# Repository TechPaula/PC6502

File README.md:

# PC6502

My 6502 project in a PC104 like form factor.  
**This is unstable, some things work and and some don't, use at your own risk of sanity and wasted money/chips**  

## Status
2025-09-08 - PCBs ordered, Parts ordered.  

2025-09-11 - Edited the firmware based on Grant Searl's code. Created this Repository  

2025-09-20 - Version 1.0 is running with a few modifications, so I've created Version 1.1 of schematics and PCB. I've added some basic examples, currently you have to copy and paste into the serial terminal. Current memory map is the same as Grants;
0000-7FFF 32K RAM
8000-9FFF FREE SPACE (8K)
A000-BFFF SERIAL INTERFACE (minimally decoded)
C000-FFFF 16K ROM (BASIC from C000 TO DED3, serial routines FF00 to FFFF)
It's also not very stable just yet. I do sometimes get corruption in the data to/from the serial console.

2025-09-21 - Version 1.1 Schematic and PCB uploaded. A lot of changes and simplicifcation in some ways, A simpler CPU board (direct link to FT245R, 74161 removed and some tidying of tracks). Fixed a couple of floating inputs to RAM/ROM
VIA is much simpler, having just the one VIA chip. POWER board has USB-PD and a 24VDC input for higher power stuff in the future. These three PCBs have been orderred.

2025-10-02 - V1.1 CPU board needed a couple of mods, I forgot that one of the pins that I used as input before had become output but the CPLD could not support that. New CPLD code done. **Now runs with a 12MHz clock (6MHz CPU speed)**, I found without the VIA it ran with a 16MHz clock fine, but would not run with a 20MHz clock, I suspect this is down to the FT245. This may get resolved when I add clock stretching to the CPLD. **VIA V1.1 working fine!** CPU board modded and Schematics and PCB updated, CPLD code for VIA and CPU updated. Updated memory map below

2025-10-11 - Power board built, works great, however the switch is inadequate, so I've hard wired it

2025-10-14 - CPLD code for the CPU PCB updated, with help from Shonky it now runs at up to the full 14MHz and also will do clock stretching when using SLOW1 line. The SLOW0 line is still bring problematic.

2025-10-16 - SPEECH synthesis chip working fine after a couple of extra wires on V1.0 of the PCB, V1.1 has been updated with these. The OPL3 (YMF262) is reading and writing, but not yet making sound.

2025-10-19 - Dual SPI board confirmed working!
It looks like my Apple II slots might be bacwards, I need to do more checking to confirm one way or the other.
The Compact Flash Storage board is also working, at least as far as raw byte reads and reads are concerned.

2025-10-23 - OPL3 Now working! I've made a change to the PCB and Schematics to fix the problem.
The CPU Board has also had a change this allows Clock stretching to be added. Currently only the SLOW1 input is working, but I will add the other later.
CPLD code for the compact flash board, updated VIA CPLD code and updated CPU CPLD code are now in.

2025-11-02 - Finished the Rev 1.0 keyboard and interface cards, I also made a simple 5V PMOD level shifter. these have been ordered.
Still testing the AII SLOT PCB, I'm unsure if it is working 100% or not, needs more time and ideally an apple II card to test with.

2025-11-12 - Working on KeyBed code.

2025-11-15 - Updated the KeyTFT board to Rev 1.1, removed the ATMEGA644, replaced it with a W65C51, as it'll only really be receiving from the keyboard I'm hoping the bug won't be a problem. The display is also now parallel rather than SPI.
Addtionally I've tweaked the CPU board to revision 1.4, this connects A15 direct to the RAM, so in theory getting more than 32K should be quicker and just require a change in the CPLD.
Keybed code working, aside from caps lock. Waiting for the full keyset and stabalisers to arrive before doing more.

2025-11-17 - EhBASIC and WozMon enhanced are now up and running on the PC6502 thanks to Shonky. EhBASIC is a little faster, but for me this brings a much needed ability to work with values in hex ($) or binary (%) which makes life a lot easier when trying to drive peripherals and IO.

2025-12-6 - I managed to get text and graphics on the display (image below), I still can't get a single pixel to work, so I'm currently using really short lines. next up will be the keyboard serial interface.

## CPU Board
Actual PCB:

Mandlebrot Code:

This board has a 6502, RAM and ROM on board, along with an ATF1502 for address decoding. There is also an FT245R which is pretending to be a 68B50 with USB. 
The CPLD code and .JED files are in /Software/CPLD

## VIA Board
This board has a single 6522 VIA and an ATF1502 for address decoding, The VIA outputs are brought out to PMOD style headers (though are 5V)
The CPLD code and .JED files are in /Software/CPLD

## Dual SPI board
Featuring two SPI interfaces, based on https://sbc.rictor.org/65spi2.html.
This uses two ATF1504AS and a single ATF1502AS.
(Note: in the picture I'm using the wrong ATF1504s, oops)

## Compact Flash board
A Very simple board in terms of electronics. Reading and Writing raw bytes is working!.

## FM(OPL3) and SPEECH card
So far the speech engine is working great, and I can read/write from/to the OPL3, I can't seem to get any sound from the OPL3 yet.

## Keybed
I kind of wanted to make my own keyboard rather than using a PS/2 keyboard, it just felt right to me.
I also had an old QDSP2118 display around, so I figured I'd pop that on there too.

## KeyTFT PCB
I wanted to use a display that fitted within the sort of cube/tower thing I've got. so I went for an off the shelf RA8875 based display, but with a parallel interface.
It uses a couple of logic level shifters as the display is 3.3V, it works really well.

### Memory Map
The memory map is subject to change in some parts, though I expect the RAM, ROM and Peripheral blocks to stay the same.

#### High Level
| Start | End | Size (Dec) | Size (Hex) | What is it | Notes |
|-------|-----|----|----|----|---------------|
| 0x0000|0x7FFF| 32768 | 0x8000 | RAM  | This is devided into sub parts below |
| 0x8000|0x9FFF|  8192 | 0x2000 | not used yet |
| 0xA000|0xBFFF|  8192 | 0x2000 | Peripherals | See table below for more info |
| 0xC000|0xFFFF| 16384 | 0x4000 | ROM | More info below |

#### RAM 
| Start | End | Size (Dec) | Size (Hex) | What is it | Notes |
|-------|-----|----|----|----|---------------|
| 0x0000|0x00FF| 256 | 0x0100 | Zero Page  | Used by the 6502 |
| 0x0100|0x02FF| 256 | 0x0100 | Stack  | Used by 6502 |
| 0x0200|0x7FFF| 32256 | 0x7E00 | User RAM  | un-allocated RAM |

#### ROM 
| Start | End | Size (Dec) | Size (Hex) | What is it | Notes |
|-------|-----|----|----|----|---------------|
| 0xC000|0xFEFF| 12288 | 0x3000 | MS Basic  | Basic Interpreter |
| 0xFF00|0xFFF9| 3584 | 0x0E00 | IO handler  | This is where common things are held, like getting input |
| 0xFFFA|0xFFFF| 6 | 0x0006 | Jump vetors  | Vectors for power on, NMI, etc |

The OS is based on Grant Searle's 6502 computer work - http://searle.x10host.com/6502/Simple6502.html
I've modified this to fit with my memory map, but it's not yet tested.
I do plan to add bits and bobs to it as I need (e.g. LOAD, SAVE, DIR).

#### Peripherals
I expect frequent changes as I add/remove things. Everything should have at least 16 bytes of address space

| Address | subAddr | RW | What is it | Notes |
|---------|---------|----|-------|---------------|
| 0xA000 | 0 - 1 | RW | Console Control/Data | 60-fake-50, mostly the same as 6850, but no config options|
| 0xA010 | 0 - 1 | RW | Keyboard iterface | a simple TTL Serial port |
| 0xA020 | 0 - 1 | RW | Serial port Control/Data | Future serial port, possibly MIDI? |
| 0xA08- | 0 - F | RW | 6522 VIA A | One of four locations |
| 0xA09- | 0 - F | RW | 6522 VIA B | Datasheet - https://eater.net/datasheets/w65c22.pdf |
| 0xA0A- | 0 - F | RW | 6522 VIA C |  |
| 0xA0B- | 0 - F | RW | 6522 VIA D |  |
| 0xA0C- | 0 - 3 | RW | SPI 0 | (shared PCB with SPI1)  |
| 0xA0D- | 0 - 3 | RW | SPI 1 | (shared PCB with SPI0)  |
| 0xA10- | 0     | W  | SP0256 speech synth | (shared PCB with OPL3) | 
| 0xA10- | 1     | RW | SP0256 speech synth status/reset || 
| 0xA11- | 0 - 3 | RW | OPL3 Chip - YM262 | (shared PCB with SP0256) | 
| 0xA20- | 0 - 7 | RW | Compact Flash |  | 
| 0xA30- | 0 - F | RW | AII SLOT 0 |  | 
| 0xA31- | 0 - F | RW | AII SLOT 1 |  | 
| 0xA32- | 0 - 1 | RW | TFT Display |  |
| 0xA33- | 0 - 3 | RW | Key Serial (6551) |  |

### Things in build & test
* **Dual Slot Apple II board**: A board that hosts Slot0 and Slot1 from an apple II, it only has the 5V rail though.
    testing is going slowly, I'm not convinced it's correct yet and I doubt it'll be 100% Apple II card compatible.
* **KeyTFT board** the TFT portion is fully working, I just need to test the keyboard interface, I'm not expecting anything difficult as it's a standard 6551 chp.

### PCBs Ordered
* ****Transputer Link Adapter/Card** and a card to host two TRAMs

## The Future
I have a bunch of things I want to try adding, some ideas I have are below, some may happen, some may not and they're not in any particular order;

* **A Complex Sound Engine**: I'm thinking of my own simple Wavetable based sound engine, possibly with analogue VCF/VCAs. Some kind of tracker software or even MIDI interface to go with it?
* **SD Storage**: I'm going to want something in the long run as retyping code is going to get tedious quickly. I have found a 6502 SPI interface here, so that may speed things up - https://sbc.rictor.org/65spi2.html
* **Some kind of HDMI grpahics adapter**: My current thinking is the videobeast (https://feertech.com/microbeast/videobeast.html) but that needs a big hole in RAM.
* **RTC & ASCII Display**: Maybe an RTC and an ascii display (I have a couple of QDSP2118 displays somewhere that I'd like to use)

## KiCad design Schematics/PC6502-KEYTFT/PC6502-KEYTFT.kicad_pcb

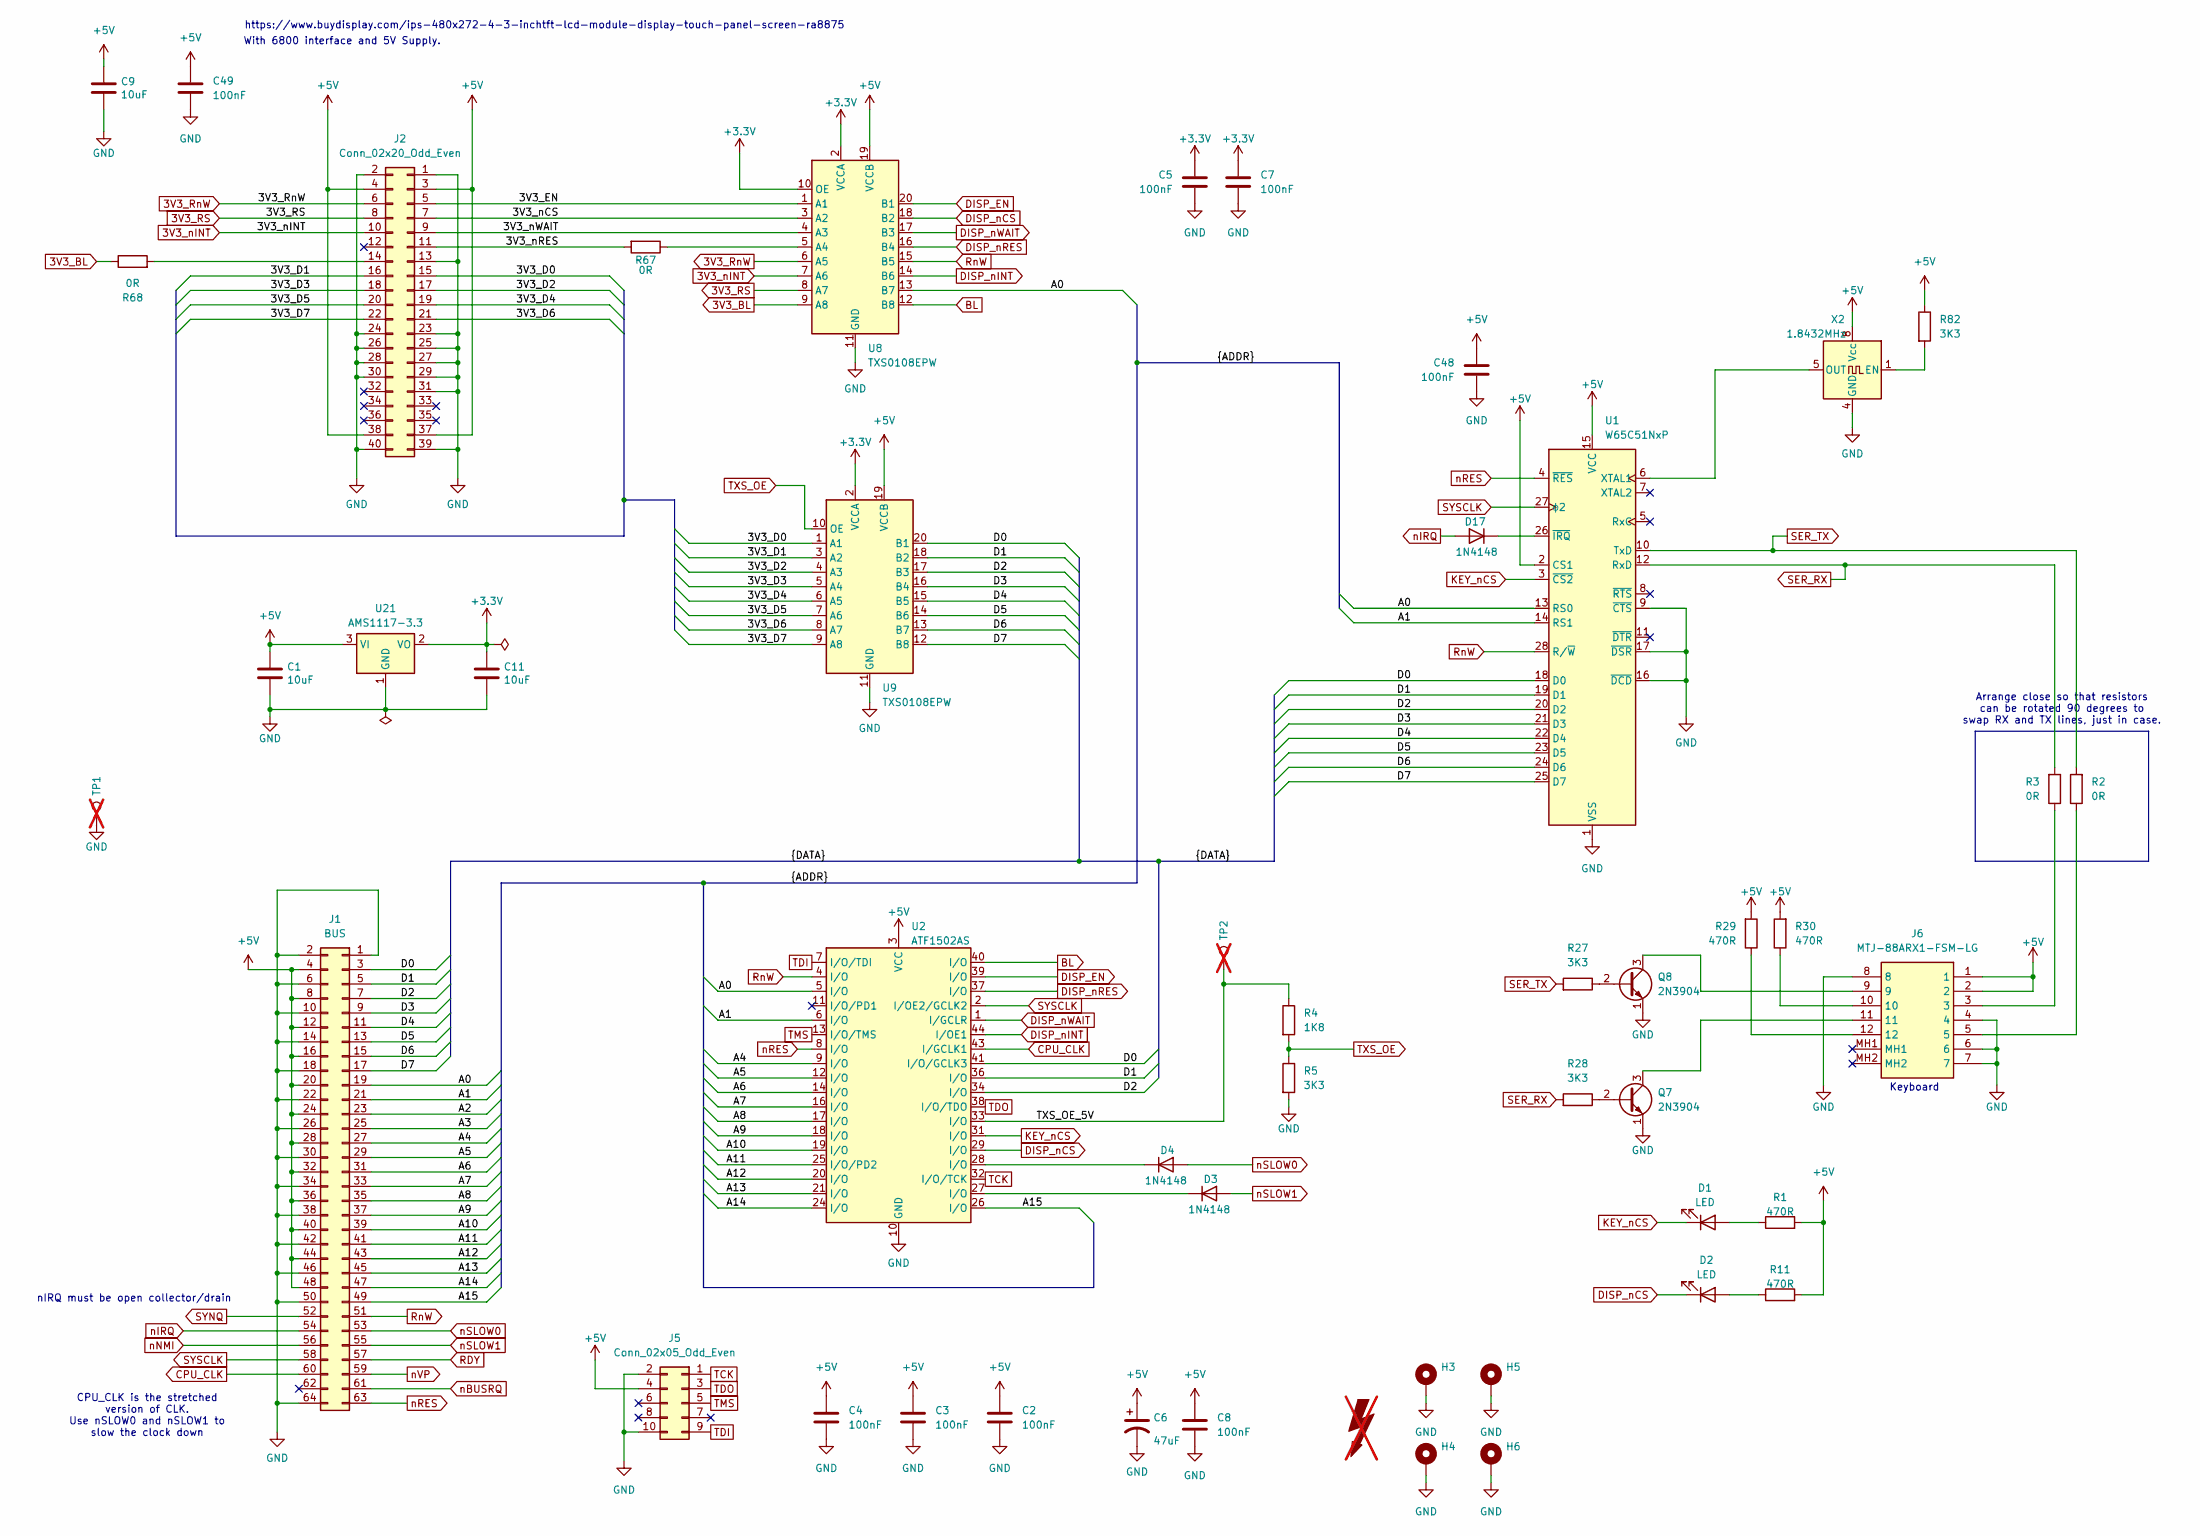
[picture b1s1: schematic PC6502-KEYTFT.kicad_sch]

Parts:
C1, C9, C11: 10uF; C_0805_2012Metric; ManufacturerPN C3216X7R1E475M085AB; LCSC C15850
C2, C3, C4, C8: 100nF; C_0603_1608Metric
C5, C7, C48, C49: 100nF; C_0603_1608Metric; LCSC C49678
C6: 47uF; C_1206_3216Metric; LCSC C96123
D1, D2: LED; LTL4221NHBP; LCSC DNF
D3, D4: 1N4148; D_DO-35_SOD27_P7.62mm_Horizontal; LCSC DNF
D17: 1N4148; D_DO-35_SOD27_P7.62mm_Horizontal
FOX1: SYM_Flash_Large; Fox_avatar_18mm; LCSC DNF; not fitted
H3, H4, H5, H6: MountingHole_Pad; MountingHole_3.2mm_M3_Pad_TopBottom; LCSC DNF
J1: BUS; PinSocket_2x32_P2.54mm_Vertical; LCSC DNF
J2: Conn_02x20_Odd_Even; PinSocket_2x20_P2.54mm_Horizontal
J5: Conn_02x05_Odd_Even; PinHeader_2x05_P2.54mm_Vertical; LCSC DNF
J6: MTJ-88ARX1-FSM-LG; MTJ88ARX1FSMLG; Mouser Part Number 737-MTJ88ARX1FSMLG
Q7, Q8: 2N3904; TO-92_Inline
R1, R11, R29, R30: 470R; R_0603_1608Metric; LCSC C23179
R2, R3: 0R; R_0603_1608Metric_Pad0.98x0.95mm_HandSolder; LCSC C23179
R4: 1K8; R_0603_1608Metric; LCSC C25890
R5, R27, R28, R82: 3K3; R_0603_1608Metric; LCSC C25890
R67, R68: 0R; R_0603_1608Metric; LCSC DNF
TP1, TP2: TestPoint; TestPoint_Loop_D1.80mm_Drill1.0mm_Beaded; LCSC DNF; not fitted
U1: W65C51NxP; DIP-28_W15.24mm
U2: ATF1502AS; PLCC-44_THT-Socket; LCSC DNF
U8, U9: TXS0108EPW; TSSOP-20_4.4x6.5mm_P0.65mm
U21: AMS1117-3.3; SOT-223-3_TabPin2; LCSC C6186
X2: 1.8432MHz; Oscillator_DIP-8; LCSC DNF

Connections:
3V3_BL: R68.1, U8.9 (A8)
3V3_RS: J2.8, U8.8 (A7)
3V3_RnW: J2.6, U8.6 (A5)
3V3_nINT: J2.10, U8.7 (A6)
+3.3V: C5.1, C7.1, C11.1, U8.2 (VCCA), U8.10 (OE), U9.2 (VCCA), U21.2 (VO)
+5V: C1.1, C2.1, C3.1, C4.1, C6.1, C8.1, C9.1, C48.1, C49.1, J1.4, J1.8, J1.12, J1.16, J1.20, J1.24, J1.28, J1.32, J1.36, J1.40, J1.44, J1.48, J2.3, J2.4, J2.37, J2.38, J5.4, J6.1, J6.2, R1.2, R11.2, R29.2, R30.2, R82.1, U1.2 (CS1), U1.15 (VCC), U2.3 (VCC), U2.15 (VCC), U2.23 (VCC), U2.35 (VCC), U8.19 (VCCB), U9.19 (VCCB), U21.3 (VI), X2.8 (Vcc)
/3V3_D0: J2.15, U9.1 (A1)
/3V3_D1: J2.16, U9.3 (A2)
/3V3_D2: J2.17, U9.4 (A3)
/3V3_D3: J2.18, U9.5 (A4)
/3V3_D4: J2.19, U9.6 (A5)
/3V3_D5: J2.20, U9.7 (A6)
/3V3_D6: J2.21, U9.8 (A7)
/3V3_D7: J2.22, U9.9 (A8)
/3V3_EN: J2.5, U8.1 (A1)
/3V3_nCS: J2.7, U8.3 (A2)
/3V3_nRES: J2.11, R67.2
/3V3_nWAIT: J2.9, U8.4 (A3)
/A0: J1.19, U1.13 (RS0), U2.5 (I/O), U8.13 (B7)
/A1: J1.21, U1.14 (RS1), U2.6 (I/O)
/A2: J1.23
/A3: J1.25
/A4: J1.27, U2.9 (I/O)
/A5: J1.29, U2.12 (I/O)
/A6: J1.31, U2.14 (I/O)
/A7: J1.33, U2.16 (I/O)
/A8: J1.35, U2.17 (I/O)
/A9: J1.37, U2.18 (I/O)
/A10: J1.39, U2.19 (I/O)
/A11: J1.41, U2.25 (I/O/PD2)
/A12: J1.43, U2.20 (I/O)
/A13: J1.45, U2.21 (I/O)
/A14: J1.47, U2.24 (I/O)
/A15: J1.49, U2.26 (I/O)
/D0: J1.3, U1.18 (D0), U2.41 (I/O/GCLK3), U9.20 (B1)
/D1: J1.5, U1.19 (D1), U2.36 (I/O), U9.18 (B2)
/D2: J1.7, U1.20 (D2), U2.34 (I/O), U9.17 (B3)
/D3: J1.9, U1.21 (D3), U9.16 (B4)
/D4: J1.11, U1.22 (D4), U9.15 (B5)
/D5: J1.13, U1.23 (D5), U9.14 (B6)
/D6: J1.15, U1.24 (D6), U9.13 (B7)
/D7: J1.17, U1.25 (D7), U9.12 (B8)
/TXS_OE_5V: R4.1, TP2.1, U2.33 (I/O)
BL: U2.40 (I/O), U8.12 (B8)
CPU_CLK: J1.60, U2.43 (I/GCLK1)
DISP_EN: U2.39 (I/O), U8.20 (B1)
DISP_nCS: D2.1 (K), U2.29 (I/O), U8.18 (B2)
DISP_nINT: U2.44 (I/OE1), U8.14 (B6)
DISP_nRES: U2.37 (I/O), U8.16 (B4)
DISP_nWAIT: U2.1 (I/GCLR), U8.17 (B3)
GND: C1.2, C2.2, C3.2, C4.2, C5.2, C6.2, C7.2, C8.2, C9.2, C11.2, C48.2, C49.2, H3.1, H4.1, H5.1, H6.1, J1.1, J1.2, J1.6, J1.10, J1.14, J1.18, J1.22, J1.26, J1.30, J1.34, J1.38, J1.42, J1.46, J1.50, J1.64, J2.1, J2.2, J2.13, J2.23, J2.24, J2.25, J2.26, J2.27, J2.28, J2.29, J2.30, J2.31, J2.39, J2.40, J5.2, J5.10, J6.4, J6.6, J6.7, J6.8, Q7.1 (E), Q8.1 (E), R5.2, TP1.1, U1.1 (VSS), U1.9 (~CTS), U1.16 (~DCD), U1.17 (~DSR), U2.10 (GND), U2.22 (GND), U2.30 (GND), U2.42 (GND), U8.11 (GND), U9.11 (GND), U21.1 (GND), X2.4 (GND)
KEY_nCS: D1.1 (K), U1.3 (~CS2), U2.31 (I/O)
unnamed: D1.2 (A), R1.1
unnamed: D2.2 (A), R11.1
unnamed: D3.1 (K), U2.27 (I/O)
unnamed: D4.1 (K), U2.28 (I/O)
unnamed: D17.1 (K), U1.26 (~IRQ)
unnamed: J2.14, R68.2
unnamed: J6.3, R3.1
unnamed: J6.5, R2.1
unnamed: J6.10, R30.1
unnamed: J6.12, R29.1
unnamed: Q7.2 (B), R28.1
unnamed: J6.11, Q7.3 (C)
unnamed: Q8.2 (B), R27.1
unnamed: J6.9, Q8.3 (C)
unnamed: U1.6 (XTAL1), X2.5 (OUT)
unnamed: R67.1, U8.5 (A4)
unnamed: R82.2, X2.1 (EN)
RDY: J1.57
RnW: J1.51, U1.28 (R/~W), U2.4 (I/O), U8.15 (B5)
SER_RX: R3.2, R28.2, U1.12 (RxD)
SER_TX: R2.2, R27.2, U1.10 (TxD)
SYNQ: J1.52
SYSCLK: J1.58, U1.27 (ϕ2), U2.2 (I/OE2/GCLK2)
TCK: J5.1, U2.32 (I/O/TCK)
TDI: J5.9, U2.7 (I/O/TDI)
TDO: J5.3, U2.38 (I/O/TDO)
TMS: J5.5, U2.13 (I/O/TMS)
TXS_OE: R4.2, R5.1, U9.10 (OE)
nBUSRQ: J1.61
nIRQ: D17.2 (A), J1.54
nNMI: J1.56
nRES: J1.63, U1.4 (~RES), U2.8 (I/O)
nSLOW0: D4.2 (A), J1.53
nSLOW1: D3.2 (A), J1.55
nVP: J1.59

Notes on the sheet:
With 6800 interface and 5V Supply.
CPU_CLK is the stretched version of CLK. Use nSLOW0 and nSLOW1 to slow the clock down
Arrange close so that resistors can be rotated 90 degrees to swap RX and TX lines, just in case.
https://www.buydisplay.com/ips-480x272-4-3-inchtft-lcd-module-display-touch-panel-screen-ra8875
Keyboard
nIRQ must be open collector/drain

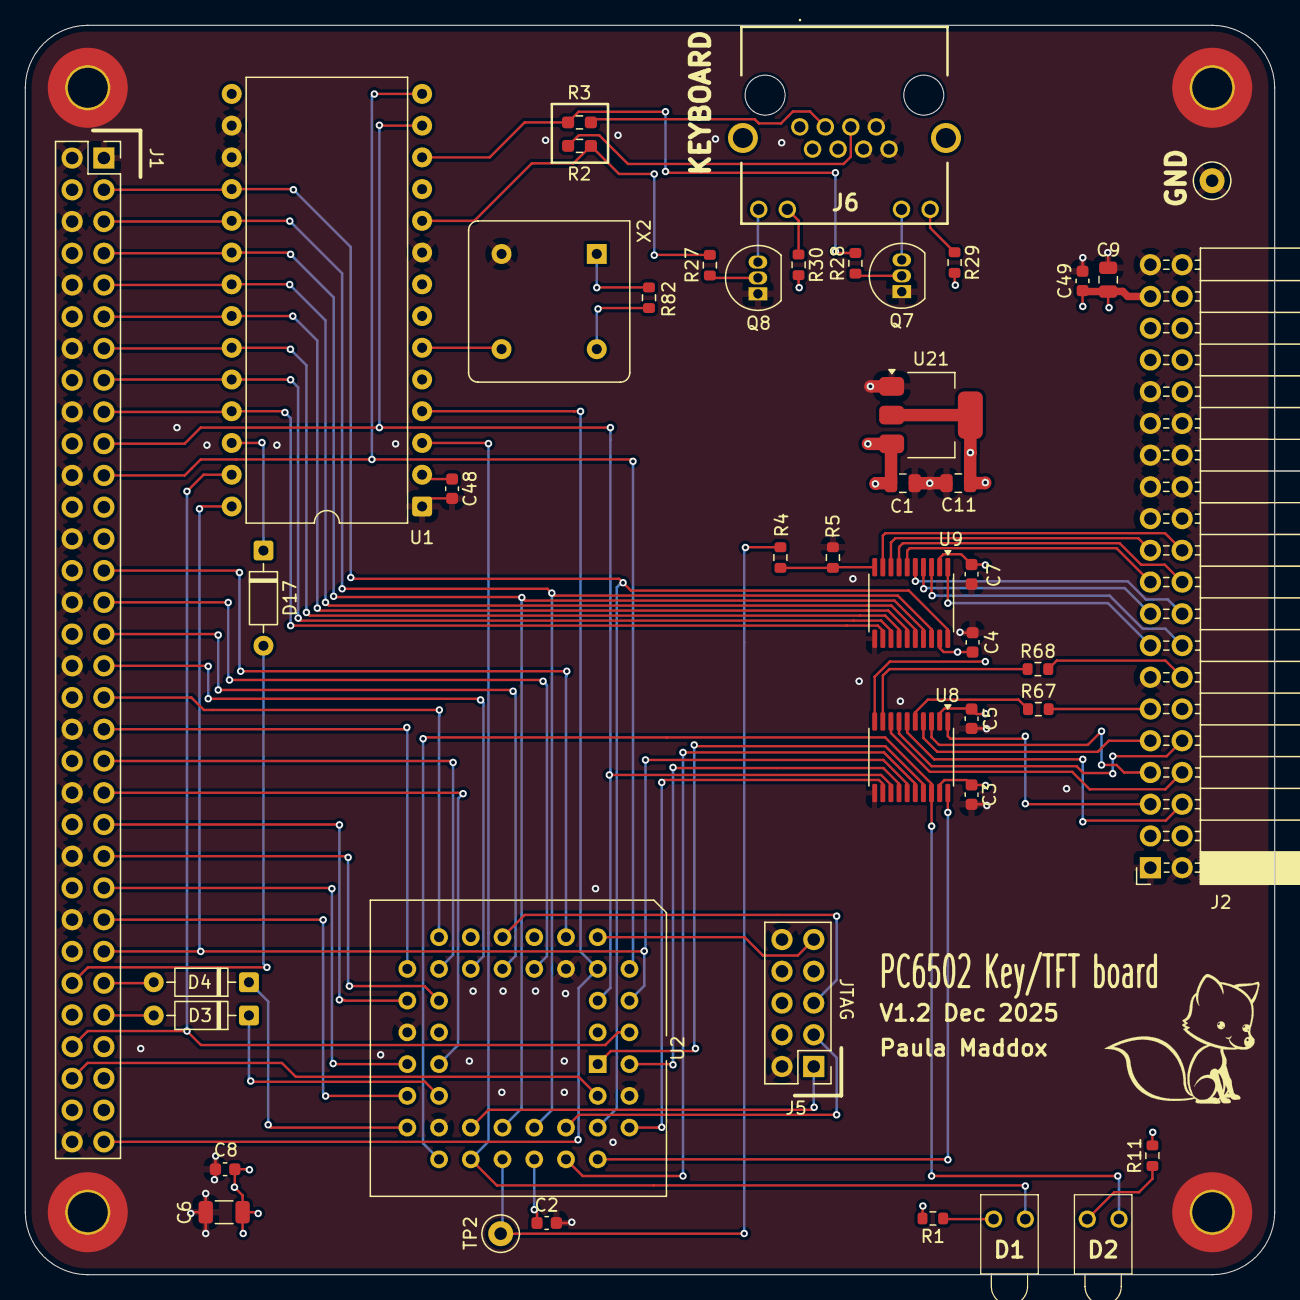
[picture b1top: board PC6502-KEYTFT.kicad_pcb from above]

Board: 4 copper layers, 100.0 x 100.0 mm, 49 parts (0 on the bottom side), 80 nets.

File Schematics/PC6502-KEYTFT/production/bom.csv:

Designator,Footprint,Quantity,Value,LCSC Part #
"C1, C11, C9",0805,3,10uF,C15850
"C2, C3, C4, C8",0603,4,100nF,
"C48, C49, C5, C7",0603,4,100nF,C49678
C6,1206,1,47uF,C96123
"D1, D2",LTL4221NHBP,2,LED,DNF
D17,D_DO-35_SOD27_P7.62mm_Horizontal,1,1N4148,
"D3, D4",D_DO-35_SOD27_P7.62mm_Horizontal,2,1N4148,DNF
"H3, H4, H5, H6",MountingHole_3.2mm_M3_Pad_TopBottom,4,MountingHole_Pad,DNF
J1,PinSocket_2x32_P2.54mm_Vertical,1,BUS,DNF
J2,PinSocket_2x20_P2.54mm_Horizontal,1,Conn_02x20_Odd_Even,
J5,PinHeader_2x05_P2.54mm_Vertical,1,Conn_02x05_Odd_Even,DNF
J6,MTJ88ARX1FSMLG,1,MTJ-88ARX1-FSM-LG,
"Q7, Q8",TO-92_Inline,2,2N3904,
"R1, R11, R29, R30",0603,4,470R,C23179
"R2, R3",0603,2,0R,C23179
"R27, R28, R82",0603,3,3K3,C25890
"R67, R68",0603,2,0R,DNF
"TP1, TP2",TestPoint_Loop_D1.80mm_Drill1.0mm_Beaded,2,TestPoint,DNF
U1,DIP-28_W15.24mm,1,W65C51NxP,
U2,PLCC-44_THT-Socket,1,ATF1502AS,DNF
U21,SOT-223-3_TabPin2,1,AMS1117-3.3,C6186
"U8, U9",TSSOP-20_4.4x6.5mm_P0.65mm,2,TXB0108PW,C53406
X2,Oscillator_DIP-8,1,1.8432MHz,DNF

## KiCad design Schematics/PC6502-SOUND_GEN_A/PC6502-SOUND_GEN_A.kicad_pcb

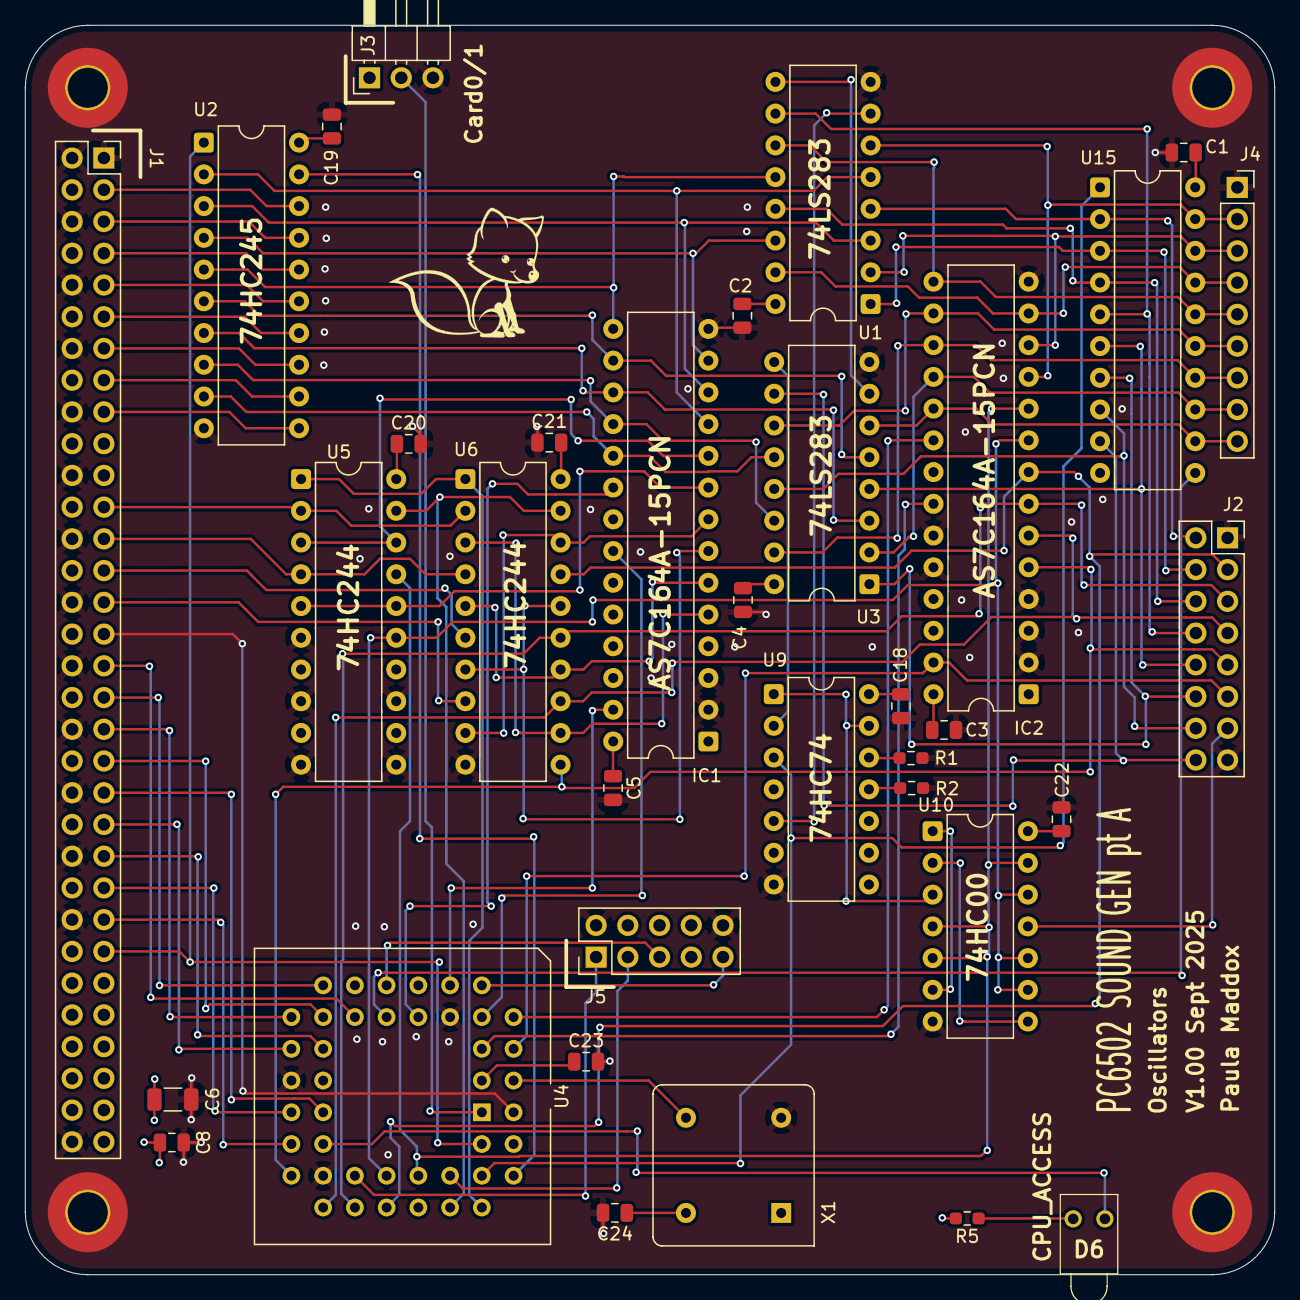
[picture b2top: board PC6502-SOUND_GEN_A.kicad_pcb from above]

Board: 4 copper layers, 100.0 x 100.0 mm, 40 parts (0 on the bottom side), 89 nets.

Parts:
C1, C2, C3, C4, C5, C8, C18, C19, C20, C21, C22, C23, C24: 100nF; C_0805_2012Metric
C6: 47uF; C_1206_3216Metric
D6: LED; LTL4221NHBP
FOX1: SYM_Flash_Large; Fox_avatar_18mm
H3, H4, H5, H6: MountingHole_Pad; MountingHole_3.2mm_M3_Pad_TopBottom
IC1, IC2: AS7C164A-15PCN; DIP-28_W7.62mm
J1: BUS; PinSocket_2x32_P2.54mm_Vertical
J2: NCO_OUT; PinSocket_2x08_P2.54mm_Vertical
J3: SND0/SND1; PinHeader_1x03_P2.54mm_Horizontal
J4: Conn_01x09; PinSocket_1x09_P2.54mm_Vertical
J5: Conn_02x05_Odd_Even; PinHeader_2x05_P2.54mm_Vertical
R1, R2: 10K; R_0603_1608Metric_Pad0.98x0.95mm_HandSolder
R5: 470R; R_0603_1608Metric_Pad0.98x0.95mm_HandSolder
U1, U3: 74LS283; DIP-16_W7.62mm
U2: 74HC245; DIP-20_W7.62mm
U4: ATF1504AS; PLCC-44_THT-Socket
U5, U6: 74AHCT244; DIP-20_W7.62mm
U9: 74HC74; DIP-14_W7.62mm
U10: 74HC00; DIP-14_W7.62mm
U15: 74HCT574; DIP-20_W7.62mm
X1: CXO_DIP8; Oscillator_DIP-8

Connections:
+5V: C1.1, C2.1, C3.1, C4.1, C5.1, C6.1, C8.1, C18.1, C19.1, C20.1, C21.1, C22.1, C23.1, C24.1, IC1.21 (A10), IC1.23 (A11), IC1.24 (A9), IC1.25 (A8), IC1.26 (CE2), IC1.28 (VCC), IC2.26 (CE2), IC2.28 (VCC), J1.4, J1.8, J1.12, J1.16, J1.20, J1.24, J1.28, J1.32, J1.36, J1.40, J1.44, J1.48, J3.1, J5.4, R5.2, U1.16 (VCC), U2.20 (VCC), U3.16 (VCC), U4.3 (VCC), U4.15 (VCC), U4.23 (VCC), U4.35 (VCC), U5.20 (VCC), U6.20 (VCC), U9.4 (~S), U9.10 (~S), U9.14 (VCC), U10.14 (VCC), U15.20 (VCC), X1.8 (Vcc)
/8BitNCO/ACC_DQ0: IC2.11 (DQ0), J4.2, U1.6 (B1), U15.19 (Q0)
/8BitNCO/ACC_DQ1: IC2.12 (DQ1), J4.3, U1.2 (B2), U15.18 (Q1)
/8BitNCO/ACC_DQ2: IC2.13 (DQ2), J4.4, U1.15 (B3), U15.17 (Q2)
/8BitNCO/ACC_DQ3: IC2.15 (DQ3), J4.5, U1.11 (B4), U15.16 (Q3)
/8BitNCO/ACC_DQ4: IC2.16 (DQ4), J4.6, U3.11 (B4), U15.15 (Q4)
/8BitNCO/ACC_DQ5: IC2.17 (DQ5), J4.7, U3.15 (B3), U15.14 (Q5)
/8BitNCO/ACC_DQ6: IC2.18 (DQ6), J4.8, U3.2 (B2), U15.13 (Q6)
/8BitNCO/ACC_DQ7: IC2.19 (DQ7), J4.9, U3.6 (B1), U15.12 (Q7)
/8BitNCO/Cin: U1.7 (C0), U9.5 (Q)
/8BitNCO/Cout: U3.9 (C4), U9.2 (D)
/8BitNCO/PTC_A0: IC1.10 (A0), U5.3 (2Y0), U5.18 (1Y0)
/8BitNCO/PTC_A1: IC1.9 (A1), U5.5 (2Y1), U5.16 (1Y1)
/8BitNCO/PTC_A2: IC1.8 (A2), U6.9 (2Y3), U6.18 (1Y0)
/8BitNCO/PTC_A3: IC1.7 (A3), U6.7 (2Y2), U6.16 (1Y1)
/8BitNCO/PTC_A4: IC1.6 (A4), U6.5 (2Y1), U6.14 (1Y2)
/8BitNCO/PTC_A5: IC1.5 (A5), U6.3 (2Y0), U6.12 (1Y3)
/8BitNCO/PTC_DQ0: IC1.11 (DQ0), U1.5 (A1), U2.2 (A0)
/8BitNCO/PTC_DQ1: IC1.12 (DQ1), U1.3 (A2), U2.3 (A1)
/8BitNCO/PTC_DQ2: IC1.13 (DQ2), U1.14 (A3), U2.4 (A2)
/8BitNCO/PTC_DQ3: IC1.15 (DQ3), U1.12 (A4), U2.5 (A3)
/8BitNCO/PTC_DQ4: IC1.16 (DQ4), U2.6 (A4), U3.5 (A1)
/8BitNCO/PTC_DQ5: IC1.17 (DQ5), U2.7 (A5), U3.3 (A2)
/8BitNCO/PTC_DQ6: IC1.18 (DQ6), U2.8 (A6), U3.14 (A3)
/8BitNCO/PTC_DQ7: IC1.19 (DQ7), U2.9 (A7), U3.12 (A4)
/8BitNCO/SUM0: J2.2, U1.4 (S1), U15.2 (D0)
/8BitNCO/SUM1: J2.4, U1.1 (S2), U15.3 (D1)
/8BitNCO/SUM2: J2.6, U1.13 (S3), U15.4 (D2)
/8BitNCO/SUM3: J2.8, U1.10 (S4), U15.5 (D3)
/8BitNCO/SUM4: J2.10, U3.4 (S1), U15.6 (D4)
/8BitNCO/SUM5: J2.12, U3.1 (S2), U15.7 (D5)
/8BitNCO/SUM6: J2.14, U3.13 (S3), U15.8 (D6)
/8BitNCO/SUM7: J2.16, U3.10 (S4), U15.9 (D7)
/A2: J1.23, U5.2 (1A0), U6.2 (1A0)
/A3: J1.25, U5.4 (1A1), U6.4 (1A1)
/A4: J1.27, U6.6 (1A2)
/A5: J1.29, U6.8 (1A3)
/A6: J1.31, U4.44 (I/OE1)
/A7: J1.33, U4.16 (I/O)
/A8: J1.35, U4.17 (I/O)
/A9: J1.37, U4.18 (I/O)
/A10: J1.39, U4.19 (I/O)
/A11: J1.41, U4.25 (I/O/PD2)
/A12: J1.43, U4.20 (I/O)
/A13: J1.45, U4.21 (I/O)
/A14: J1.47, U4.24 (I/O)
/A15: J1.49, U4.26 (I/O)
/D0: J1.3, U2.18 (B0)
/D1: J1.5, U2.17 (B1)
/D2: J1.7, U2.16 (B2)
/D3: J1.9, U2.15 (B3)
/D4: J1.11, U2.14 (B4)
/D5: J1.13, U2.13 (B5)
/D6: J1.15, U2.12 (B6)
/D7: J1.17, U2.11 (B7)
/nWAVE_VALID: J2.13, U10.11
/nZERO_CARRY: U9.1 (~R), U9.13 (~R), U10.3
ACC_nCS: IC2.20 (CE#), U4.6 (I/O)
ACC_nOE: IC2.22 (OE#), U4.5 (I/O)
ACC_nWR: IC2.27 (WE#), J2.11, U4.4 (I/O)
BYTE_SEL_A0: IC2.10 (A0), U4.36 (I/O), U5.17 (2A0), U10.4, U10.5, U10.13
BYTE_SEL_A1: IC2.9 (A1), U4.34 (I/O), U5.15 (2A1), U10.9, U10.10, U10.12
GND: C1.2, C2.2, C3.2, C4.2, C5.2, C6.2, C8.2, C18.2, C19.2, C20.2, C21.2, C22.2, C23.2, C24.2, H3.1, H4.1, H5.1, H6.1, IC1.2 (A12), IC1.3 (A7), IC1.4 (A6), IC1.14 (VSS), IC2.2 (A12), IC2.3 (A7), IC2.4 (A6), IC2.14 (VSS), IC2.21 (A10), IC2.23 (A11), IC2.24 (A9), IC2.25 (A8), J1.1, J1.2, J1.6, J1.10, J1.14, J1.18, J1.22, J1.26, J1.30, J1.34, J1.38, J1.42, J1.46, J1.50, J1.64, J2.1, J2.15, J3.3, J4.1, J5.2, J5.10, R1.2, R2.2, U1.8 (GND), U2.10 (GND), U3.8 (GND), U4.10 (GND), U4.22 (GND), U4.30 (GND), U4.42 (GND), U5.6 (1A2), U5.8 (1A3), U5.10 (GND), U5.11 (2A3), U5.13 (2A2), U6.10 (GND), U9.7 (GND), U10.7 (GND), U15.10 (GND), X1.4 (GND)
NCO_ADDR_nEN: U4.37 (I/O), U5.19 (2OE), U6.19 (2OE)
NCO_CLK: U4.2 (I/OE2/GCLK2), X1.5 (OUT)
unnamed: D6.2 (A), R5.1
unnamed: D6.1 (K), U4.27 (I/O)
unnamed: J3.2, U4.1 (I/GCLR)
unnamed: U1.9 (C4), U3.7 (C0)
unnamed: R2.1, U9.11 (C)
unnamed: R1.1, U9.12 (D)
unnamed: U10.1, U10.6
unnamed: U10.2, U10.8
OSC_A0: IC2.8 (A2), J2.3, U4.33 (I/O), U6.17 (2A0)
OSC_A1: IC2.7 (A3), J2.5, U4.31 (I/O), U6.15 (2A1)
OSC_A2: IC2.6 (A4), J2.7, U4.29 (I/O), U6.13 (2A2)
OSC_A3: IC2.5 (A5), J2.9, U4.28 (I/O), U6.11 (2A3)
PTC_nCS: IC1.20 (CE#), U4.12 (I/O)
PTC_nOE: IC1.22 (OE#), U4.8 (I/O)
PTC_nWR: IC1.27 (WE#), U4.9 (I/O)
RnW: J1.51, U2.1 (A->B), U4.43 (I/GCLK1)
SUM_BUFF_CK: U4.14 (I/O), U15.11 (Cp)
SUM_BUFF_nOE: U4.41 (I/O/GCLK3), U9.3 (C), U15.1 (OE)
SYS_ADDR_nEN: U4.39 (I/O), U5.1 (1OE), U6.1 (1OE)
TCK: J5.1, U4.32 (I/O/TCK)
TDI: J5.9, U4.7 (I/O/TDI)
TDO: J5.3, U4.38 (I/O/TDO)
TMS: J5.5, U4.13 (I/O/TMS)
nSYSDATA_TO_PTC: U2.19 (CE), U4.40 (I/O)

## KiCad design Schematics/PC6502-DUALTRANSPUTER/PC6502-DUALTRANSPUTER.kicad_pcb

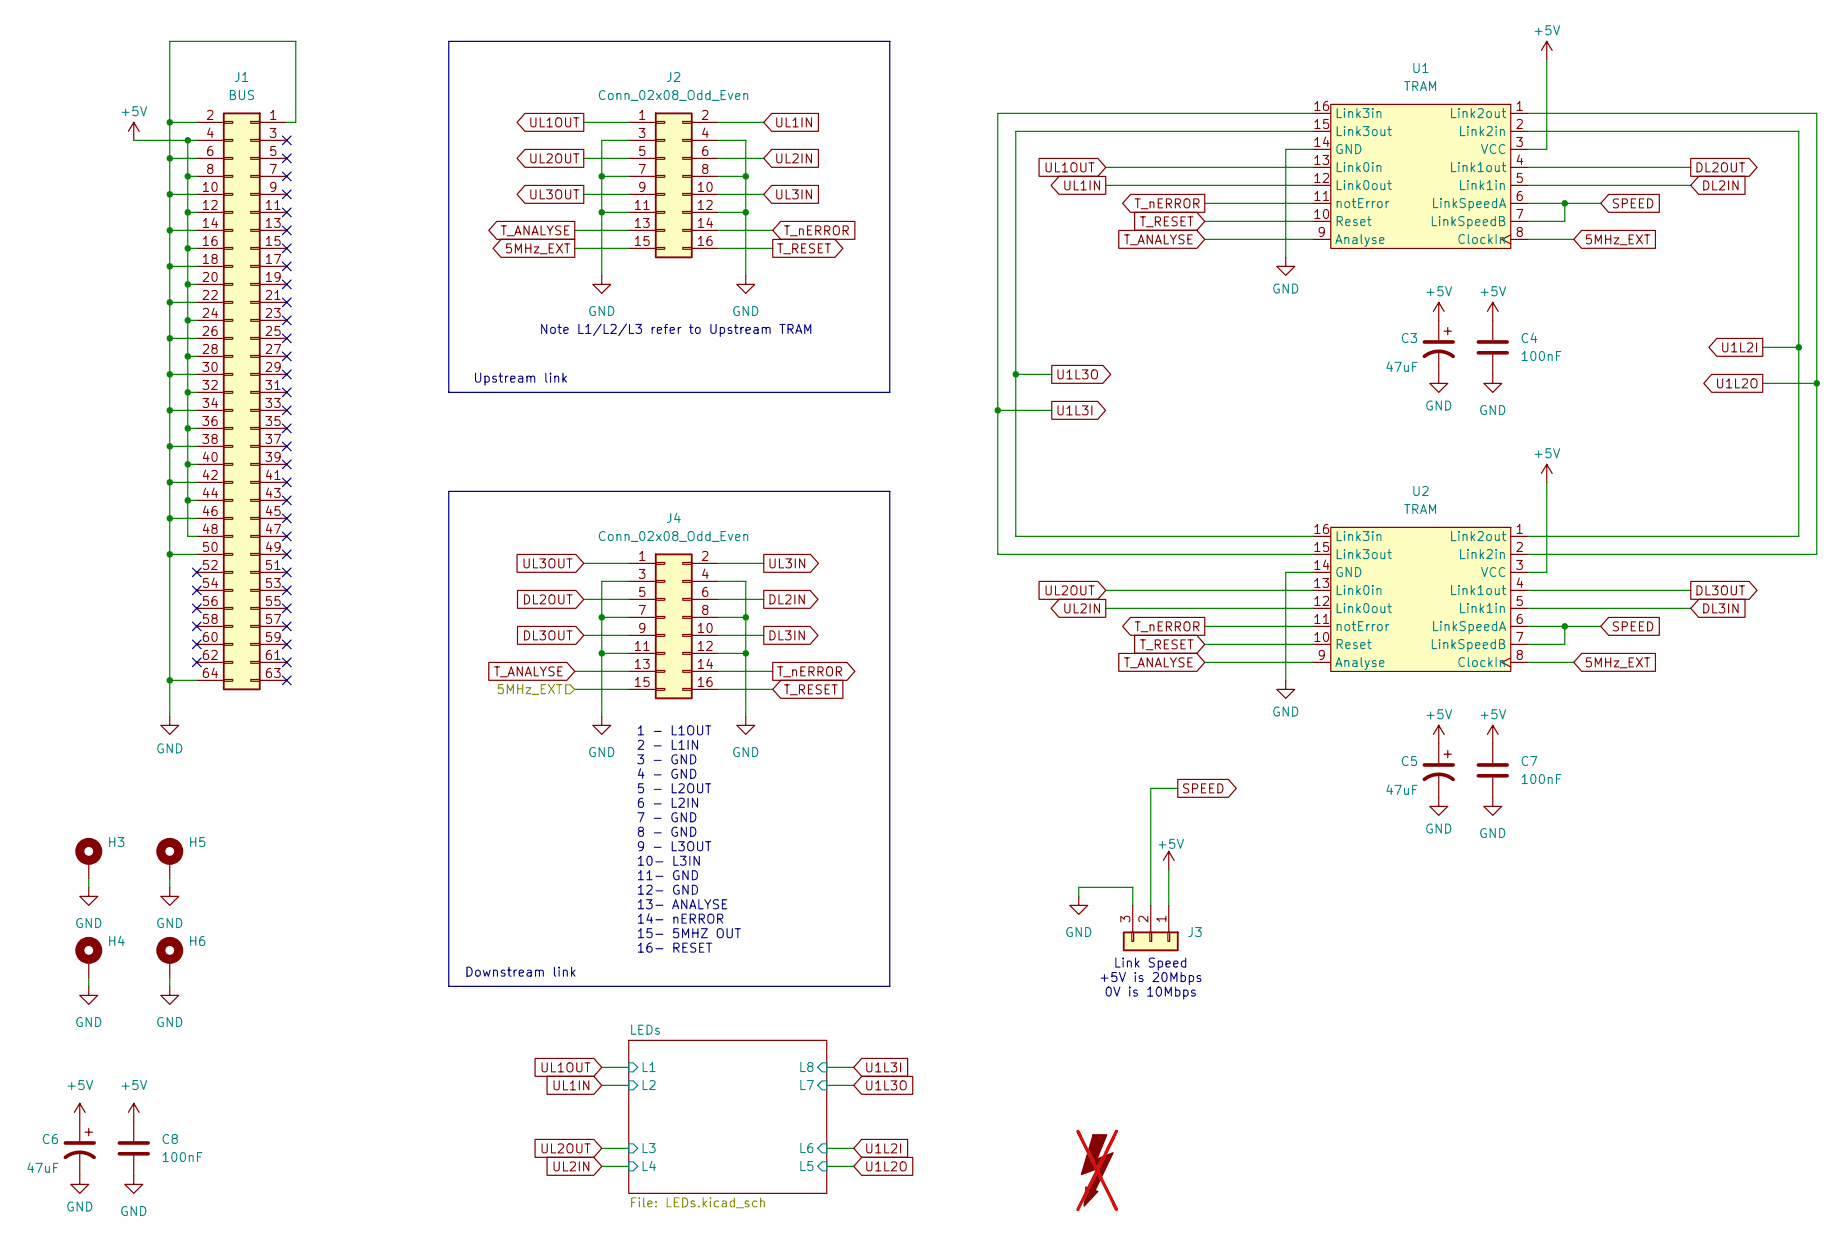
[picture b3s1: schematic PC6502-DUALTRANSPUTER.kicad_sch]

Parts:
C3, C5, C6: 47uF; C_1206_3216Metric; LCSC C96123
C4, C7: 100nF; C_0603_1608Metric
C8: 100nF; C_0805_2012Metric
FOX1: SYM_Flash_Large; Fox_avatar_18mm; LCSC DNF; not fitted
H3, H4, H5, H6: MountingHole_Pad; MountingHole_3.2mm_M3_Pad_TopBottom; LCSC DNF
J1: BUS; PinSocket_2x32_P2.54mm_Vertical; LCSC DNF
J2, J4: Conn_02x08_Odd_Even; PinHeader_2x08_P2.54mm_Horizontal
J3: Conn_01x03; PinHeader_1x03_P2.54mm_Horizontal
U1, U2: TRAM

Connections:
5MHz_EXT: J2.15, J4.15, U1.8 (ClockIn), U2.8 (ClockIn)
+5V: C3.1, C4.1, C5.1, C6.1, C7.1, C8.1, J1.4, J1.8, J1.12, J1.16, J1.20, J1.24, J1.28, J1.32, J1.36, J1.40, J1.44, J1.48, J3.1, U1.3 (VCC), U2.3 (VCC); also elsewhere on the board
DL2IN: J4.6, U1.5 (Link1in)
DL2OUT: J4.5, U1.4 (Link1out)
DL3IN: J4.10, U2.5 (Link1in)
DL3OUT: J4.9, U2.4 (Link1out)
GND: C3.2, C4.2, C5.2, C6.2, C7.2, C8.2, H3.1, H4.1, H5.1, H6.1, J1.1, J1.2, J1.6, J1.10, J1.14, J1.18, J1.22, J1.26, J1.30, J1.34, J1.38, J1.42, J1.46, J1.50, J1.64, J2.3, J2.4, J2.7, J2.8, J2.11, J2.12, J3.3, J4.3, J4.4, J4.7, J4.8, J4.11, J4.12, U1.14 (GND), U2.14 (GND); also elsewhere on the board
SPEED: J3.2, U1.6 (LinkSpeedA), U1.7 (LinkSpeedB), U2.6 (LinkSpeedA), U2.7 (LinkSpeedB)
T_ANALYSE: J2.13, J4.13, U1.9 (Analyse), U2.9 (Analyse)
T_RESET: J2.16, J4.16, U1.10 (Reset), U2.10 (Reset)
T_nERROR: J2.14, J4.14, U1.11 (notError), U2.11 (notError)
U1L2I: U1.2 (Link2in), U2.1 (Link2out); also elsewhere on the board
U1L2O: U1.1 (Link2out), U2.2 (Link2in); also elsewhere on the board
U1L3I: U1.16 (Link3in), U2.15 (Link3out); also elsewhere on the board
U1L3O: U1.15 (Link3out), U2.16 (Link3in); also elsewhere on the board
UL1IN: J2.2, U1.12 (Link0out); also elsewhere on the board
UL1OUT: J2.1, U1.13 (Link0in); also elsewhere on the board
UL2IN: J2.6, U2.12 (Link0out); also elsewhere on the board
UL2OUT: J2.5, U2.13 (Link0in); also elsewhere on the board
UL3IN: J2.10, J4.2
UL3OUT: J2.9, J4.1

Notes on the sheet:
Upstream link
1 - L1OUT 2 - L1IN 3 - GND 4 - GND 5 - L2OUT 6 - L2IN 7 - GND 8 - GND 9 - L3OUT 10- L3IN 11- GND 12- GND 13- ANALYSE 14- nERROR 15- 5MHZ OUT 16- RESET
Link Speed +5V is 20Mbps 0V is 10Mbps
Downstream link
Note L1/L2/L3 refer to Upstream TRAM

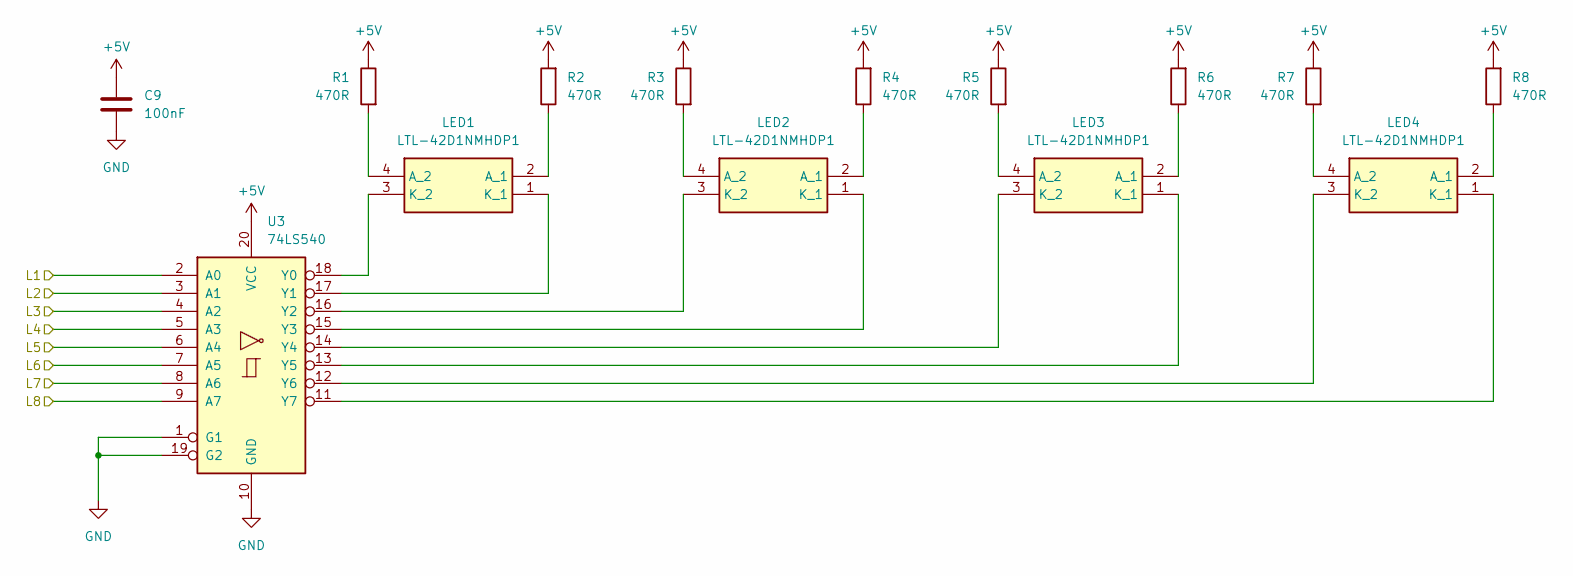
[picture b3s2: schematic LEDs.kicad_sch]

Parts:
C9: 100nF; C_0603_1608Metric
LED1, LED2, LED3, LED4: LTL-42D1NMHDP1; LTL42D1NMHDP1; Mouser Part Number 859-LTL-42D1NMHDP1
R1, R2, R3, R4, R5, R6, R7, R8: 470R; R_0603_1608Metric_Pad0.98x0.95mm_HandSolder; LCSC C23179
U3: 74LS540; TSSOP-20_4.4x6.5mm_P0.65mm

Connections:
+5V: C9.1, R1.1, R2.2, R3.1, R4.2, R5.1, R6.2, R7.1, R8.2, U3.20 (VCC); also elsewhere on the board
GND: C9.2, U3.1 (G1), U3.10 (GND), U3.19 (G2); also elsewhere on the board
unnamed: LED1.2 (A_1), R2.1
unnamed: LED1.4 (A_2), R1.2
unnamed: LED1.1 (K_1), U3.17 (Y1)
unnamed: LED1.3 (K_2), U3.18 (Y0)
unnamed: LED2.2 (A_1), R4.1
unnamed: LED2.4 (A_2), R3.2
unnamed: LED2.1 (K_1), U3.15 (Y3)
unnamed: LED2.3 (K_2), U3.16 (Y2)
unnamed: LED3.2 (A_1), R6.1
unnamed: LED3.4 (A_2), R5.2
unnamed: LED3.1 (K_1), U3.13 (Y5)
unnamed: LED3.3 (K_2), U3.14 (Y4)
unnamed: LED4.2 (A_1), R8.1
unnamed: LED4.4 (A_2), R7.2
unnamed: LED4.1 (K_1), U3.11 (Y7)
unnamed: LED4.3 (K_2), U3.12 (Y6)
U1L2I: U3.7 (A5); also elsewhere on the board
U1L2O: U3.6 (A4); also elsewhere on the board
U1L3I: U3.8 (A6); also elsewhere on the board
U1L3O: U3.9 (A7); also elsewhere on the board
UL1IN: U3.3 (A1); also elsewhere on the board
UL1OUT: U3.2 (A0); also elsewhere on the board
UL2IN: U3.5 (A3); also elsewhere on the board
UL2OUT: U3.4 (A2); also elsewhere on the board
